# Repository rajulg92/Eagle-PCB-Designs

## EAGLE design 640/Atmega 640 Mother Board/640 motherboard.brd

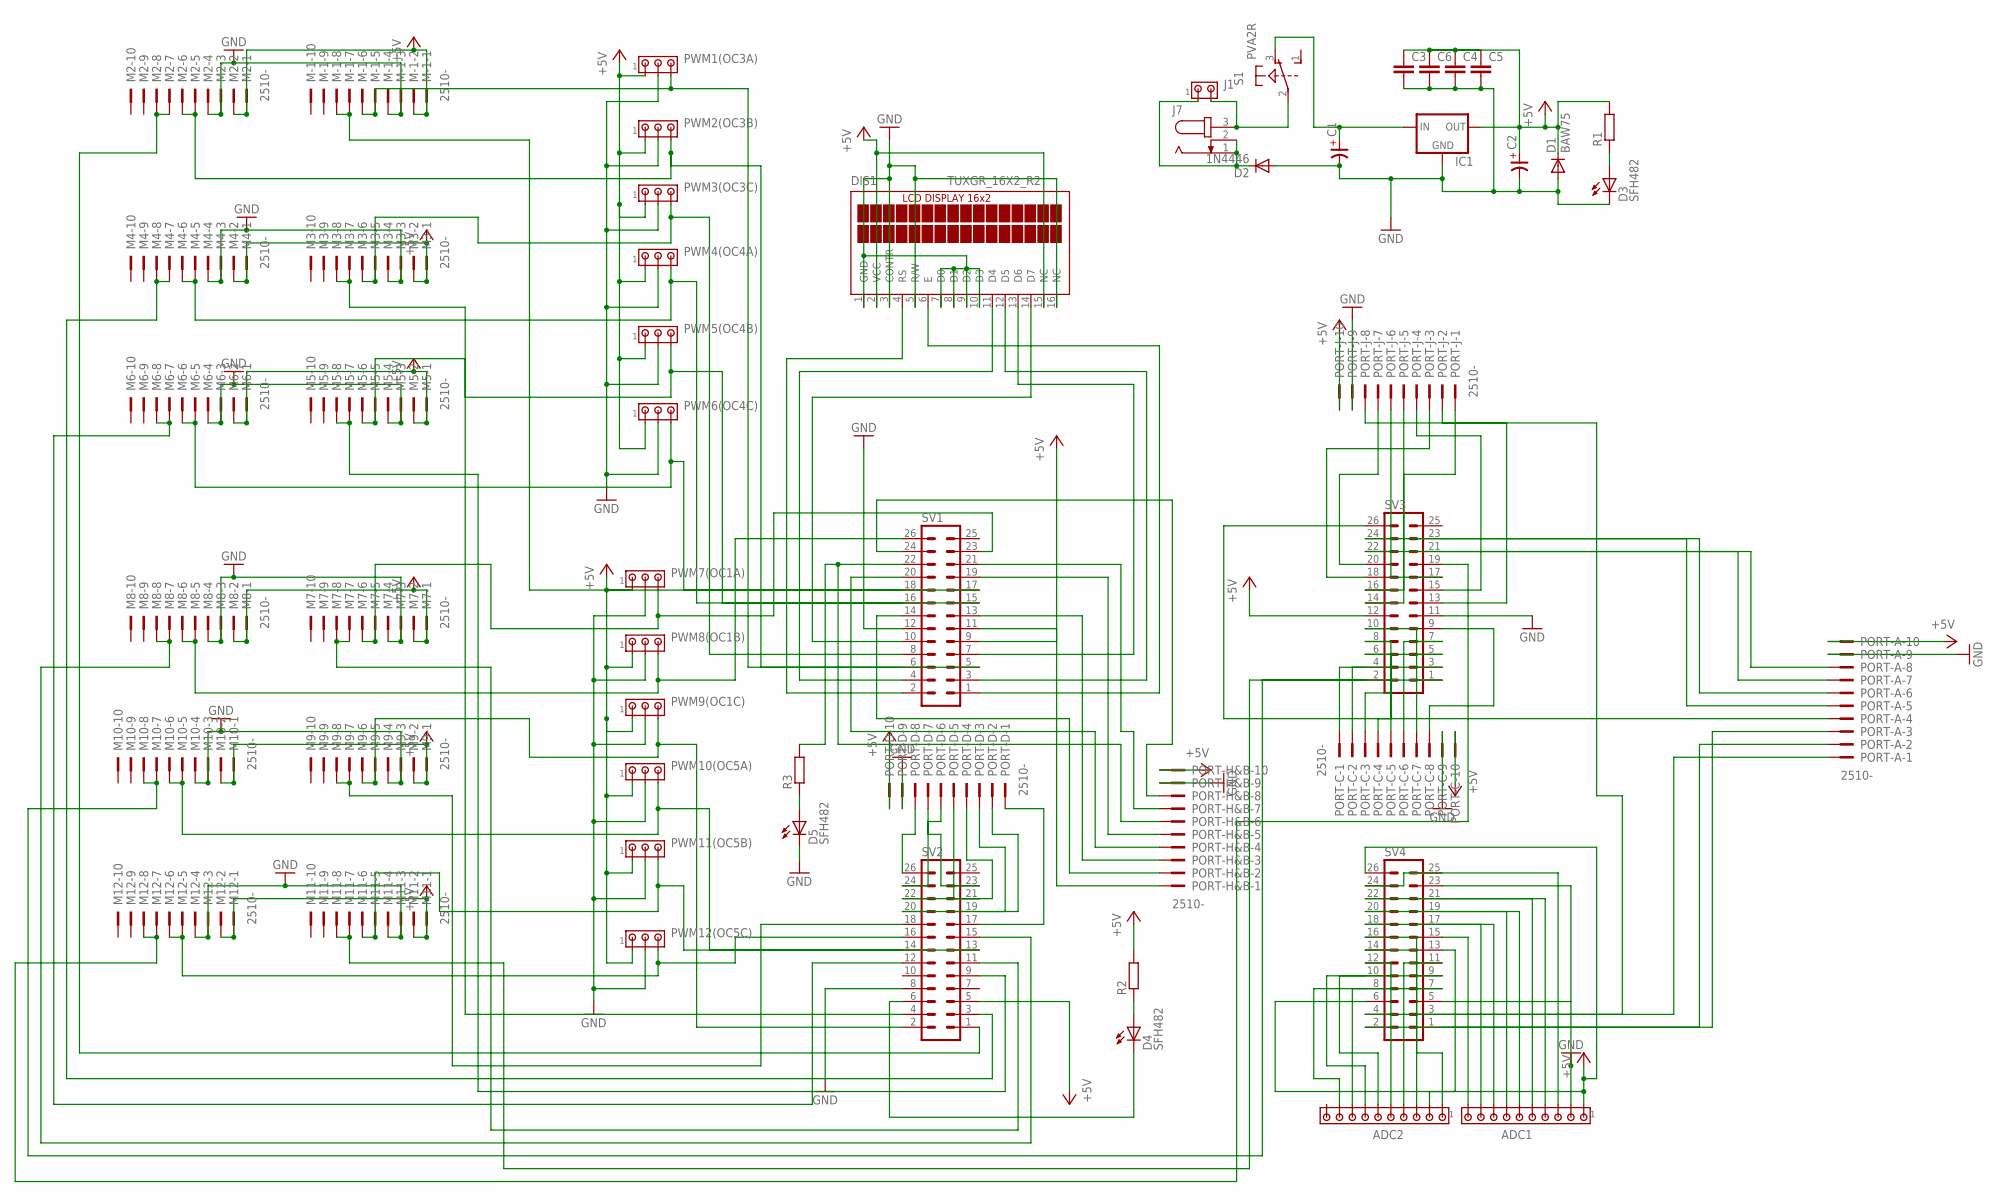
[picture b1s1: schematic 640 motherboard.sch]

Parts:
ADC1, ADC2: MTA10-100; 10X10MTA
C1, C2: CP-E-050X125; E-050X125
C3, C4, C5, C6: C2.5/2; C2.5-2
D1: BAW75; DO35-10
D2: 1N4446; DO35-10
D3, D4, D5: SFH482
DIS1: TUXGR_16X2_R2
IC1: LM323-TO3; TO3-K02
J1: MTA02-156; 1X2MTA
J7: JACK-PLUG1; SPC4078
M2, M3, M4, M5, M6, M7, M8, M9, M10, M11, M12: 2510-; PAK100/2500-10
M-1: 2510-; PAK100/2500-10
PORT-A: 2510-; PAK100/2500-10
PORT-C: 2510-; PAK100/2500-10
PORT-D: 2510-; PAK100/2500-10
PORT-H&B: 2510-; PAK100/2500-10
PORT-J: 2510-; PAK100/2500-10
PWM1(OC3A), PWM2(OC3B), PWM3(OC3C), PWM4(OC4A), PWM5(OC4B), PWM6(OC4C), PWM7(OC1A), PWM8(OC1B), PWM9(OC1C), PWM10(OC5A), PWM11(OC5B), PWM12(OC5C): MTA03-100; 10X03MTA
R1, R2, R3: R-EU_0207/10; 0207/10
S1: PVA2R
SV1, SV2, SV3, SV4: ML26

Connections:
+5V: ADC1.1, C2.+, C3.1, C4.1, C5.1, C6.1, D1.C, DIS1.2 (VCC), DIS1.15 (NC), IC1.1 (OUT), M2.1, M2.2, M3.1, M3.2, M4.1, M4.2, M5.1, M5.2, M6.1, M6.2, M7.1, M7.2, M8.1, M8.2, M9.1, M9.2, M10.1, M10.2, M11.1, M11.2, M12.1, M12.2, M-1.1, M-1.2, PORT-A.10, PORT-C.10, PORT-D.10, PORT-H&B.10, PORT-J.10, PWM1(OC3A).1, PWM2(OC3B).1, PWM3(OC3C).1, PWM4(OC4A).1, PWM5(OC4B).1, PWM6(OC4C).1, PWM7(OC1A).1, PWM8(OC1B).1, PWM9(OC1C).1, PWM10(OC5A).1, PWM11(OC5B).1, PWM12(OC5C).1, R1.2, R2.2, SV1.9, SV2.5, SV3.12, SV4.6, SV4.26
GND: ADC1.2, C1.-, C2.-, C3.2, C4.2, C5.2, C6.2, D1.A, D2.A, D3.K (C), D5.K (C), DIS1.1 (GND), DIS1.3 (CONTR), DIS1.5 (R/W), DIS1.7 (D0), DIS1.8 (D1), DIS1.9 (D2), DIS1.10 (D3), DIS1.16 (NC), IC1.3 (GND), M2.3, M2.4, M3.3, M3.4, M4.3, M4.4, M5.3, M5.4, M6.3, M6.4, M7.3, M7.4, M8.3, M8.4, M9.3, M9.4, M10.3, M10.4, M11.3, M11.4, M12.3, M12.4, M-1.3, M-1.4, PORT-A.9, PORT-C.9, PORT-D.9, PORT-H&B.9, PORT-J.9, PWM1(OC3A).2, PWM2(OC3B).2, PWM3(OC3C).2, PWM4(OC4A).2, PWM5(OC4B).2, PWM6(OC4C).2, PWM7(OC1A).2, PWM8(OC1B).2, PWM9(OC1C).2, PWM10(OC5A).2, PWM11(OC5B).2, PWM12(OC5C).2, SV1.12, SV2.8, SV3.11, SV4.5, SV4.23
unnamed: C1.+, IC1.2 (IN), S1.3 (O)
unnamed: D2.C, J1.1, J7.1, J7.2
unnamed: PORT-C.1, SV3.4
unnamed: M2.5, M2.6, PWM2(OC3B).3, SV1.5
unnamed: M3.5, M3.6, PWM3(OC3C).3, SV1.8
unnamed: M4.5, M4.6, PWM4(OC4A).3, SV1.16
unnamed: M5.5, M5.6, PWM5(OC4B).3, SV1.15
unnamed: M6.5, M6.6, PWM6(OC4C).3, SV1.18
unnamed: M12.5, M12.6, PWM12(OC5C).3, SV2.16
unnamed: PORT-C.2, SV3.3
unnamed: M10.5, M10.6, PWM10(OC5A).3, SV2.14
unnamed: M9.5, M9.6, PWM9(OC1C).3, SV2.2
unnamed: M8.5, M8.6, PWM8(OC1B).3, SV1.26
unnamed: M7.5, M7.6, PWM7(OC1A).3, SV1.23
unnamed: ADC1.4, SV4.21
unnamed: ADC1.5, SV4.22
unnamed: ADC1.3, SV4.24
unnamed: ADC1.6, SV4.19
unnamed: ADC1.7, SV4.20
unnamed: ADC1.8, SV4.17
unnamed: ADC1.9, SV4.18
unnamed: ADC1.10, SV4.15
unnamed: ADC2.1, SV4.16
unnamed: ADC2.2, SV4.13
unnamed: ADC2.3, SV4.14
unnamed: ADC2.4, SV4.11
unnamed: ADC2.5, SV4.12
unnamed: ADC2.7, SV4.10
unnamed: ADC2.6, SV4.9
unnamed: ADC2.9, SV4.8
unnamed: M-1.5, M-1.6, PWM1(OC3A).3, SV1.6
unnamed: M11.5, M11.6, PWM11(OC5B).3, SV2.13
unnamed: PORT-C.3, SV3.6
unnamed: PORT-C.4, SV3.5
unnamed: PORT-C.5, SV3.8
unnamed: PORT-C.6, SV3.7
unnamed: PORT-C.7, SV3.10
unnamed: PORT-C.8, SV3.9
unnamed: PORT-J.1, SV3.14
unnamed: PORT-J.2, SV3.13
unnamed: PORT-J.3, SV3.16
unnamed: PORT-J.4, SV3.15
unnamed: PORT-J.5, SV3.18
unnamed: PORT-J.6, SV3.17
unnamed: PORT-J.7, SV3.20
unnamed: PORT-J.8, SV4.3
unnamed: ADC2.8, SV4.7
unnamed: PORT-A.1, SV4.4
unnamed: PORT-A.2, SV4.1
unnamed: PORT-A.3, SV4.2
unnamed: PORT-A.4, SV3.26
unnamed: PORT-A.5, SV3.23
unnamed: PORT-A.6, SV3.24
unnamed: PORT-A.7, SV3.21
unnamed: PORT-A.8, SV3.22
unnamed: PORT-D.8, SV2.26
unnamed: PORT-D.7, SV2.23
unnamed: PORT-D.6, SV2.24
unnamed: PORT-D.5, SV2.21
unnamed: PORT-D.2, SV2.20
unnamed: PORT-D.3, SV2.19
unnamed: PORT-D.4, SV2.22
unnamed: PORT-D.1, SV2.17
unnamed: D3.A, R1.1
unnamed: J1.2, J7.3, S1.2
unnamed: DIS1.11 (D4), SV1.4
unnamed: DIS1.12 (D5), SV1.3
unnamed: DIS1.13 (D6), SV1.7
unnamed: DIS1.14 (D7), SV1.10
unnamed: DIS1.4 (RS), SV1.2
unnamed: DIS1.6 (E), SV1.1
unnamed: PORT-H&B.1, SV1.11
unnamed: M2.7, M2.8, SV2.1
unnamed: PORT-H&B.2, SV1.14
unnamed: PORT-H&B.3, SV1.13
unnamed: PORT-H&B.4, SV1.20
unnamed: M3.7, M3.8, SV2.4
unnamed: PORT-H&B.5, SV1.19
unnamed: M-1.7, M-1.8, SV1.17
unnamed: M5.7, M5.8, SV2.9
unnamed: M4.7, M4.8, SV2.3
unnamed: PORT-H&B.6, R3.2, SV1.22
unnamed: PORT-H&B.7, SV1.21
unnamed: M7.7, M7.8, SV2.11
unnamed: M6.7, M6.8, SV2.12
unnamed: PORT-H&B.8, SV1.24
unnamed: D4.A, R2.1
unnamed: M9.7, M9.8, SV2.18
unnamed: M8.7, M8.8, SV2.15
unnamed: M11.7, M11.8, SV3.1
unnamed: D4.K (C), SV2.6
unnamed: M10.7, M10.8, SV3.2
unnamed: M12.7, M12.8, SV3.19
unnamed: D5.A, R3.1

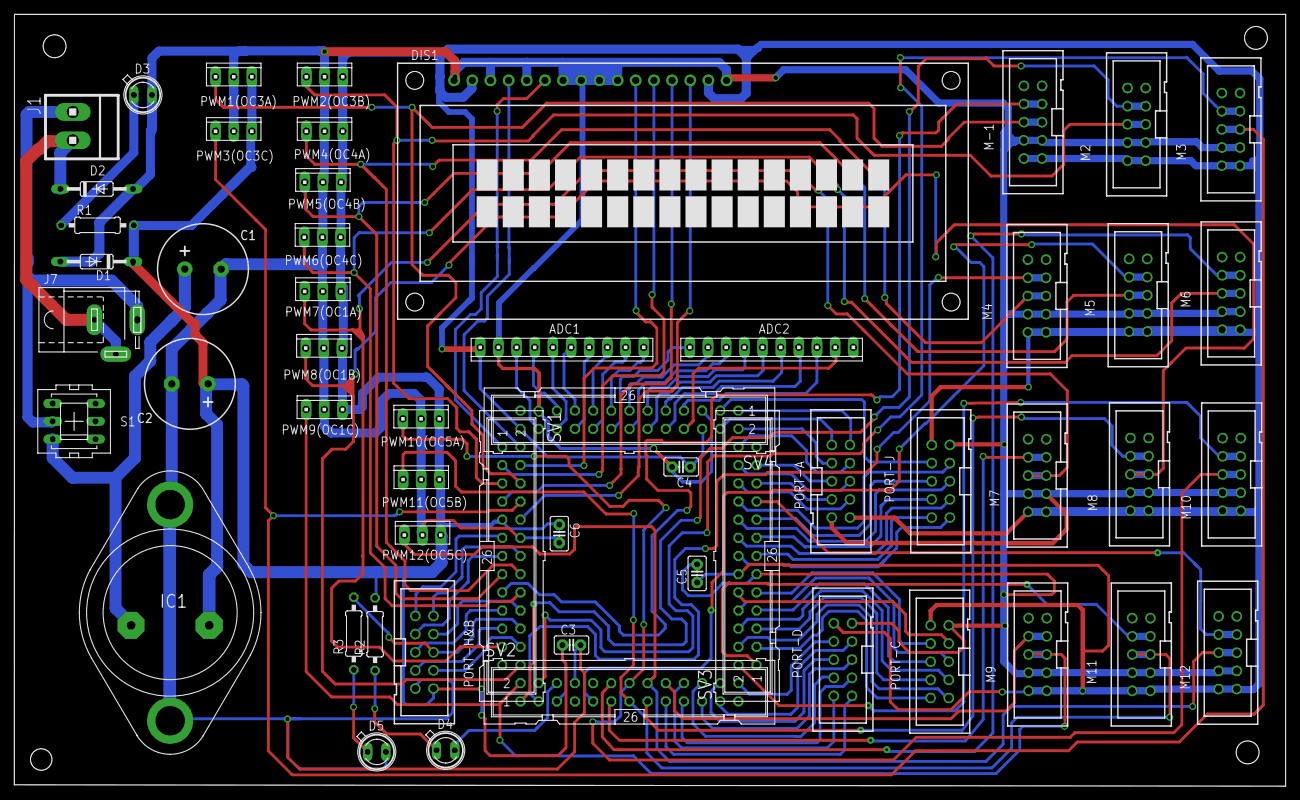
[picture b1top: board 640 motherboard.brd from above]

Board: 2 copper layers, 177.8 x 107.9 mm, 54 parts (0 on the bottom side), 96 nets.

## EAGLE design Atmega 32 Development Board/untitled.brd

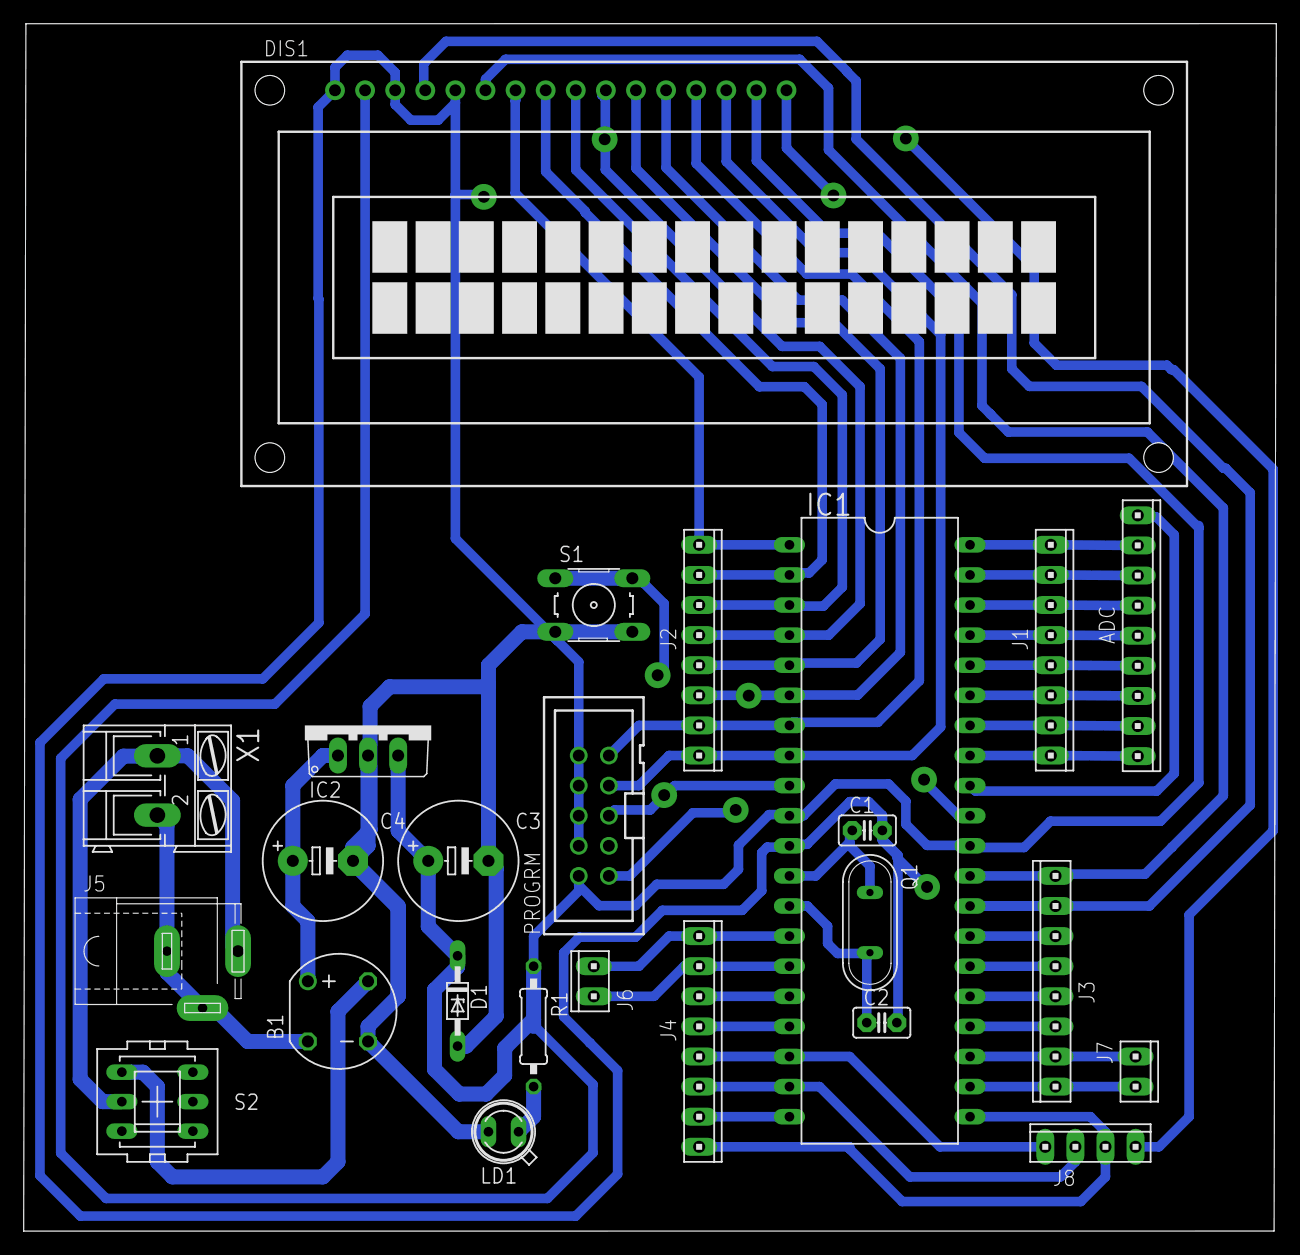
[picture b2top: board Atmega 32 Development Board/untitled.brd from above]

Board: 2 copper layers, 105.7 x 101.9 mm, 25 parts (0 on the bottom side), 43 nets.

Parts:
ADC: 10X09MTA
B1: RB1A
C1, C2: C2.5-2
C3, C4: E5-10,5
D1: BZX90; DO34Z7
DIS1: TUXGR_16X2_R2
IC1: MEGA323-P; DIL40
IC2: 7805TV; TO220V
J1, J2, J3, J4: 10X08MTA
J5: SPC4078
J6, J7: 10X02MTA
J8: 10X04MTA
LD1: SFH482
PROGRM: 2510-; PAK100/2500-10
Q1: QS
R1: 0207/10
S1: B3F-10XX
S2: PVA2R
X1: AK300/2

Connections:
GND: B1.-, C1.2, C2.2, C3.-, C4.-, D1.A, DIS1.1, DIS1.3, DIS1.5, DIS1.16, IC1.11, IC1.31, IC2.2, LD1.K, PROGRM.4, PROGRM.6, PROGRM.8, PROGRM.10, S1.3, S1.4
unnamed: B1.AC2, J5.1, J5.2, X1.2
unnamed: J5.3, S2.2, X1.1
unnamed: B1.AC1, S2.1
unnamed: B1.+, C4.+, IC2.1
unnamed: ADC.9, IC1.32
unnamed: DIS1.14, IC1.8, J2.1, PROGRM.7
unnamed: C1.1, IC1.12, Q1.1
unnamed: C2.1, IC1.13, Q1.2
unnamed: DIS1.13, IC1.7, J2.2, PROGRM.9
unnamed: ADC.1, IC1.33, J1.1
unnamed: ADC.2, IC1.34, J1.2
unnamed: ADC.3, IC1.35, J1.3
unnamed: ADC.4, IC1.36, J1.4
unnamed: ADC.5, IC1.37, J1.5
unnamed: ADC.6, IC1.38, J1.6
unnamed: ADC.7, IC1.39, J1.7
unnamed: ADC.8, IC1.40, J1.8
unnamed: DIS1.11, IC1.5, J2.4
unnamed: DIS1.10, IC1.4, J2.5, J8.1
unnamed: DIS1.9, IC1.3, J2.6
unnamed: DIS1.8, IC1.2, J2.7
unnamed: DIS1.7, IC1.1, J2.8
unnamed: DIS1.6, IC1.29, J3.1
unnamed: DIS1.4, IC1.28, J3.2
unnamed: IC1.27, J3.3
unnamed: IC1.26, J3.4
unnamed: IC1.25, J3.5
unnamed: IC1.24, J3.6
unnamed: IC1.23, J3.7, J7.2
unnamed: IC1.22, J3.8, J7.1
unnamed: IC1.21, J4.1, J8.2
unnamed: IC1.20, J4.2
unnamed: IC1.19, J4.3, J8.3
unnamed: IC1.18, J4.4, J8.4
unnamed: IC1.17, J4.5
unnamed: IC1.16, J4.6
unnamed: IC1.15, J4.7, J6.2
unnamed: IC1.14, J4.8, J6.1
unnamed: IC1.9, PROGRM.5, S1.1, S1.2
unnamed: DIS1.12, IC1.6, J2.3, PROGRM.1
unnamed: LD1.A, R1.2
VCC: C3.+, D1.C, DIS1.2, DIS1.15, IC1.10, IC1.30, IC2.3, PROGRM.2, R1.1

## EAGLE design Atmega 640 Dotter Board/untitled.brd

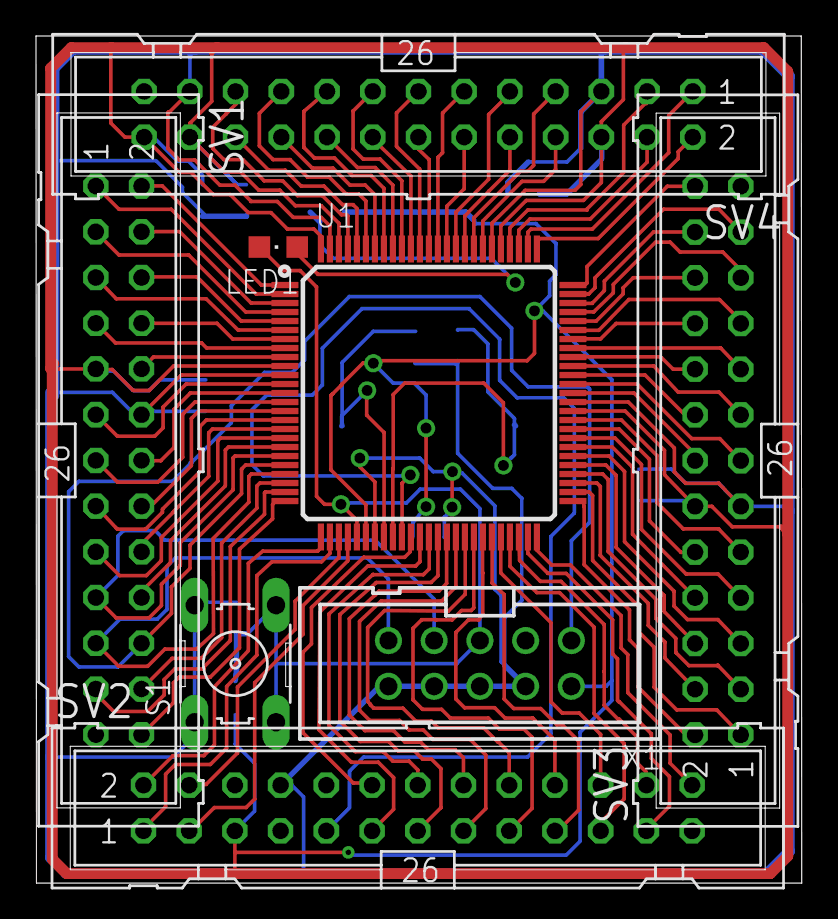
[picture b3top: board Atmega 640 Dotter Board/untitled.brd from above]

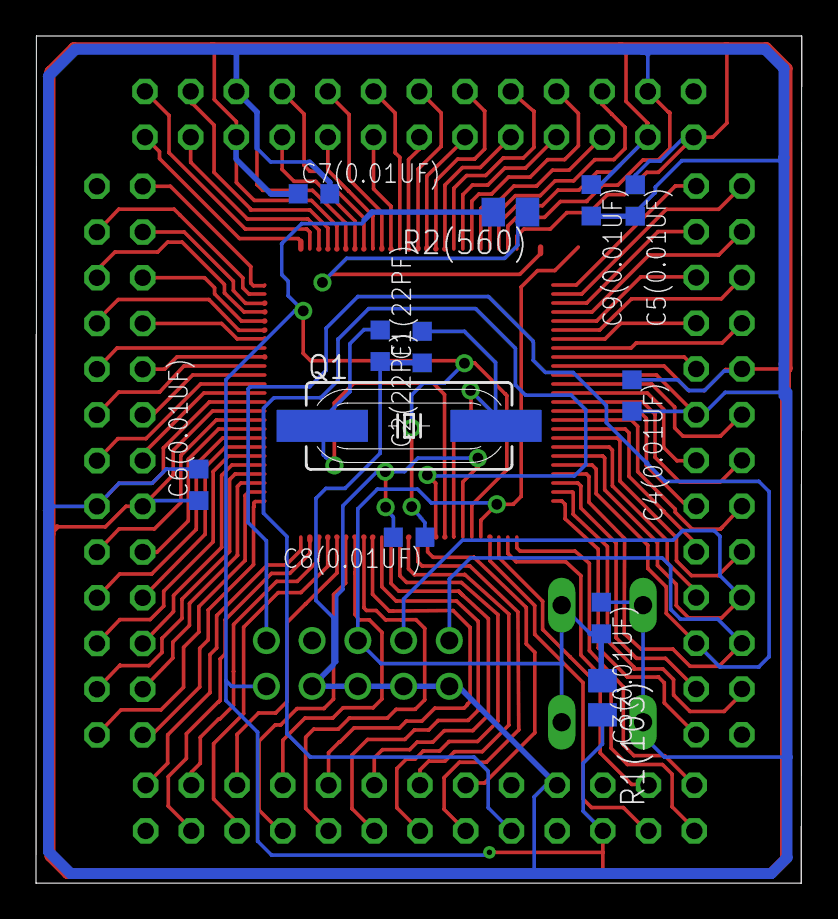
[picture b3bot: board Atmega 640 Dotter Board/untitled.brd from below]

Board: 2 copper layers, 42.5 x 47.1 mm, 20 parts (12 on the bottom side), 92 nets.

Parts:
C1(22PF), C2(22PF), C3(0.01UF), C4(0.01UF), C5(0.01UF), C6(0.01UF), C7(0.01UF), C8(0.01UF), C9(0.01UF): C0603K
LED1: CHIPLED_0805
Q1: SM49
R1(103), R2(560): M2012
S1: B3F-10XX
SV1, SV2, SV3, SV4: ML26
U1: TQFP100
X1: 2510-; PAK100/2500-10

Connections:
unnamed: SV3.14, U1.63
unnamed: C2(22PF).1, Q1.1, U1.34
unnamed: SV2.16, U1.40
unnamed: SV1.20, U1.19
unnamed: SV1.1, U1.2
unnamed: SV3.13, U1.64
unnamed: SV1.3, U1.4
unnamed: SV1.4, U1.3
unnamed: SV1.6, U1.5
unnamed: SV1.5, U1.6
unnamed: SV1.8, U1.7
unnamed: SV1.7, U1.8
unnamed: SV1.10, U1.9
unnamed: SV1.19, U1.20, X1.7
unnamed: SV1.11, U1.12
unnamed: SV1.14, U1.13
unnamed: SV1.13, U1.14
unnamed: SV1.16, U1.15
unnamed: SV1.15, U1.16
unnamed: SV1.18, U1.17
unnamed: SV1.17, U1.18
unnamed: SV1.22, U1.21, X1.1
unnamed: SV1.21, U1.22, X1.9
unnamed: SV1.24, U1.23
unnamed: SV1.23, U1.24
unnamed: SV1.26, U1.25
unnamed: SV2.2, U1.26
unnamed: SV2.1, U1.27
unnamed: SV2.4, U1.28
unnamed: SV2.3, U1.29
unnamed: SV2.9, U1.35
unnamed: SV2.12, U1.36
unnamed: SV2.11, U1.37
unnamed: SV2.14, U1.38
unnamed: SV2.13, U1.39
unnamed: SV2.15, U1.41
unnamed: SV2.18, U1.42
unnamed: SV2.17, U1.43
unnamed: SV2.20, U1.44
unnamed: SV2.19, U1.45
unnamed: SV2.22, U1.46
unnamed: SV2.21, U1.47
unnamed: SV2.24, U1.48
unnamed: SV2.23, U1.49
unnamed: SV2.26, U1.50
unnamed: C1(22PF).2, Q1.2, U1.33
unnamed: SV3.2, U1.51
unnamed: SV3.1, U1.52
unnamed: SV3.4, U1.53
unnamed: SV3.3, U1.54
unnamed: SV3.6, U1.55
unnamed: SV3.5, U1.56
unnamed: SV3.8, U1.57
unnamed: SV3.7, U1.58
unnamed: SV3.10, U1.59
unnamed: SV3.9, U1.60
unnamed: SV4.18, U1.92
unnamed: SV3.16, U1.65
unnamed: SV3.15, U1.66
unnamed: SV3.18, U1.67
unnamed: SV3.17, U1.68
unnamed: SV3.20, U1.69
unnamed: SV3.19, U1.70
unnamed: SV3.22, U1.71
unnamed: SV3.21, U1.72
unnamed: SV3.24, U1.73
unnamed: SV3.23, U1.74
unnamed: SV3.26, U1.75
unnamed: SV4.2, U1.76
unnamed: SV4.1, U1.77
unnamed: SV4.4, U1.78
unnamed: SV4.3, U1.79
unnamed: SV4.19, U1.95
unnamed: SV4.7, U1.83
unnamed: SV4.8, U1.82
unnamed: SV4.9, U1.85
unnamed: SV4.10, U1.84
unnamed: SV4.11, U1.87
unnamed: SV4.12, U1.86
unnamed: SV4.13, U1.89
unnamed: SV4.14, U1.88
unnamed: SV4.15, U1.91
unnamed: SV4.16, U1.90
unnamed: SV4.17, U1.93
unnamed: SV4.20, U1.94
unnamed: SV4.21, U1.97
unnamed: SV4.22, U1.96
unnamed: C4(0.01UF).1, C5(0.01UF).1, C6(0.01UF).1, C7(0.01UF).1, C8(0.01UF).1, C9(0.01UF).1, R1(103).2, R2(560).2, SV1.9, SV2.5, SV3.12, SV4.6, SV4.24, SV4.26, U1.10, U1.31, U1.61, U1.80, U1.98, U1.100, X1.2
unnamed: SV1.2, U1.1
unnamed: C3(0.01UF).2, LED1.C, R1(103).1, S1.3, S1.4, U1.30, X1.5
unnamed: C1(22PF).1, C2(22PF).2, C3(0.01UF).1, C4(0.01UF).2, C5(0.01UF).2, C6(0.01UF).2, C7(0.01UF).2, C8(0.01UF).2, C9(0.01UF).2, S1.1, S1.2, SV1.12, SV2.8, SV3.11, SV4.5, SV4.23, U1.11, U1.32, U1.62, U1.81, U1.99, X1.4, X1.6, X1.8, X1.10
unnamed: LED1.A, R2(560).1

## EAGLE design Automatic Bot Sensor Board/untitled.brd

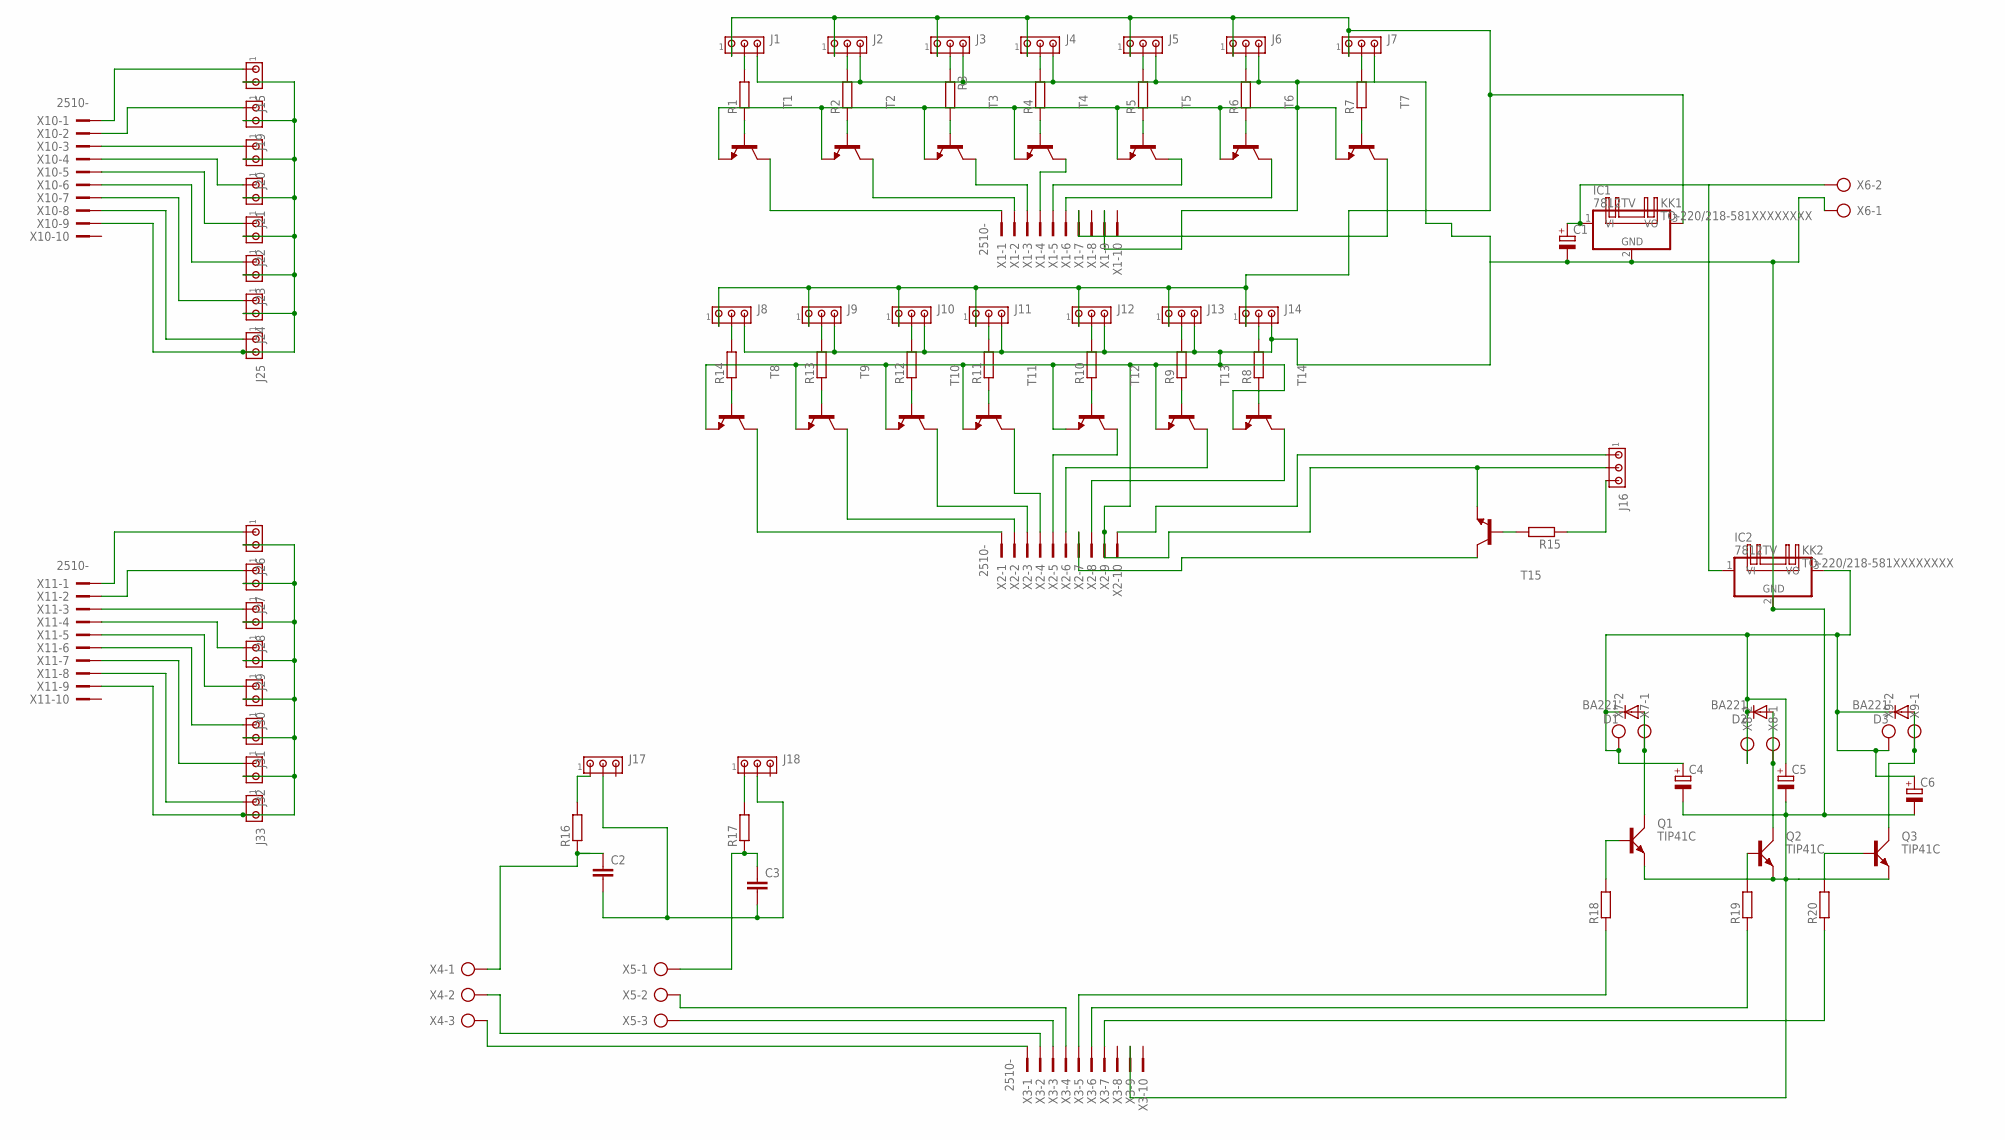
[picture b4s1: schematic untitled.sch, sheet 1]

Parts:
C1: CPOL-EUE5-10.5; E5-10,5
C2, C3: C-EU375-192X418; C375-192X418
C4, C5, C6: CPOL-EUE5-13; E5-13
D1, D2, D3: BA221; DO35-10
IC1, IC2: 7812TV; TO220V
J1, J2, J3, J4, J5, J6, J7, J8, J9, J10, J11, J12, J13, J14, J16, J17, J18: MTA03-100; 10X03MTA
J15, J19, J20, J21, J22, J23, J24, J25, J26, J27, J28, J29, J30, J31, J32, J33: MTA02-100; 10X02MTA
KK1, KK2: TO-220/218-581XXXXXXXX; 581XXXXXXXX
Q1, Q2, Q3: TIP41C; TO220AV
R1, R2, R3, R4, R5, R6, R7, R8, R9, R10, R11, R12, R13, R14, R15, R16, R17, R18, R19, R20: R-EU_0207/10; 0207/10
T1, T2, T3, T4, T5, T6, T7, T8, T9, T10, T11, T12, T13, T14, T15: 2N5401-NPN-TO92-CBE; TO92-CBE
X1, X2, X3, X10, X11: 2510-; PAK100/2500-10
X4, X5: AK300/3
X6, X7, X8, X9: AK300/2

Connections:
unnamed: R3.2, T3.B
unnamed: R1.1, T1.B
unnamed: J2.2, R2.2
unnamed: J8.2, R14.2
unnamed: J1.2, R1.2
unnamed: R2.1, T2.B
unnamed: J3.2, R3.1
unnamed: J4.2, R4.2
unnamed: R4.1, T4.B
unnamed: R5.1, T5.B
unnamed: J5.2, R5.2
unnamed: J6.2, R6.2
unnamed: R6.1, T6.B
unnamed: J7.2, R7.2
unnamed: R7.1, T7.B
unnamed: J13.2, R9.2
unnamed: R9.1, T13.B
unnamed: R8.1, T14.B
unnamed: J14.2, R8.2
unnamed: J12.2, R10.2
unnamed: R10.1, T12.B
unnamed: R11.1, T11.B
unnamed: J11.2, R11.2
unnamed: J10.2, R12.2
unnamed: R12.1, T10.B
unnamed: R13.1, T9.B
unnamed: J9.2, R13.2
unnamed: R14.1, T8.B
unnamed: T5.C, X1.5
unnamed: T8.C, X2.1
unnamed: T9.C, X2.2
unnamed: T1.C, X1.1
unnamed: T10.C, X2.3
unnamed: T11.C, X2.4
unnamed: T12.C, X2.5
unnamed: T13.C, X2.6
unnamed: J16.1, X2.10
unnamed: T2.C, X1.2
unnamed: T3.C, X1.3
unnamed: T4.C, X1.4
unnamed: T6.C, X1.6
unnamed: T7.C, X1.7
unnamed: D1.A, Q1.C, X7.1
unnamed: IC1.3 (VO), J1.1, J2.1, J3.1, J4.1, J5.1, J6.1, J7.1, J8.1, J9.1, J10.1, J11.1, J12.1, J13.1, J14.1
unnamed: T14.C, X2.8
unnamed: C1.+, IC1.1 (VI), IC2.1 (VI), X6.2
unnamed: J16.3, R15.1
unnamed: R15.2, T15.B
unnamed: T15.C, X2.7
unnamed: Q1.B, R18.2
unnamed: D2.A, Q2.C, X8.1
unnamed: Q2.B, R19.2
unnamed: Q3.B, R20.2
unnamed: C1.-, C4.-, C5.-, C6.-, IC1.2 (GND), IC2.2 (GND), J1.3, J2.3, J3.3, J4.3, J5.3, J6.3, J7.3, J8.3, J9.3, J10.3, J11.3, J12.3, J13.3, J14.3, J16.2, Q1.E, Q2.E, Q3.E, T1.E, T2.E, T3.E, T4.E, T5.E, T6.E, T7.E, T8.E, T9.E, T10.E, T11.E, T12.E, T13.E, T14.E, T15.E, X1.9, X2.9, X3.9, X6.1
unnamed: D3.A, Q3.C, X9.1
unnamed: J17.1, R16.2
unnamed: C4.+, C5.+, C6.+, D1.C, D2.C, D3.C, IC2.3 (VO), X7.2, X8.2, X9.2
unnamed: C2.1, R16.1, X4.1
unnamed: J18.1, R17.2
unnamed: C3.1, R17.1, X5.1
unnamed: C2.2, C3.2, J17.2, J18.2
unnamed: J15.1, X10.1
unnamed: J19.1, X10.2
unnamed: X3.1, X4.3
unnamed: X3.2, X4.2
unnamed: X3.3, X5.3
unnamed: X3.4, X5.2
unnamed: R18.1, X3.5
unnamed: R19.1, X3.6
unnamed: R20.1, X3.7
unnamed: J20.1, X10.3
unnamed: J21.1, X10.4
unnamed: J22.1, X10.5
unnamed: J23.1, X10.6
unnamed: J24.1, X10.7
unnamed: J25.1, X10.8
unnamed: J15.2, J19.2, J20.2, J21.2, J22.2, J23.2, J24.2, J25.2, X10.9
unnamed: J26.1, X11.1
unnamed: J27.1, X11.2
unnamed: J28.1, X11.3
unnamed: J29.1, X11.4
unnamed: J30.1, X11.5
unnamed: J31.1, X11.6
unnamed: J32.1, X11.7
unnamed: J33.1, X11.8
unnamed: J26.2, J27.2, J28.2, J29.2, J30.2, J31.2, J32.2, J33.2, X11.9

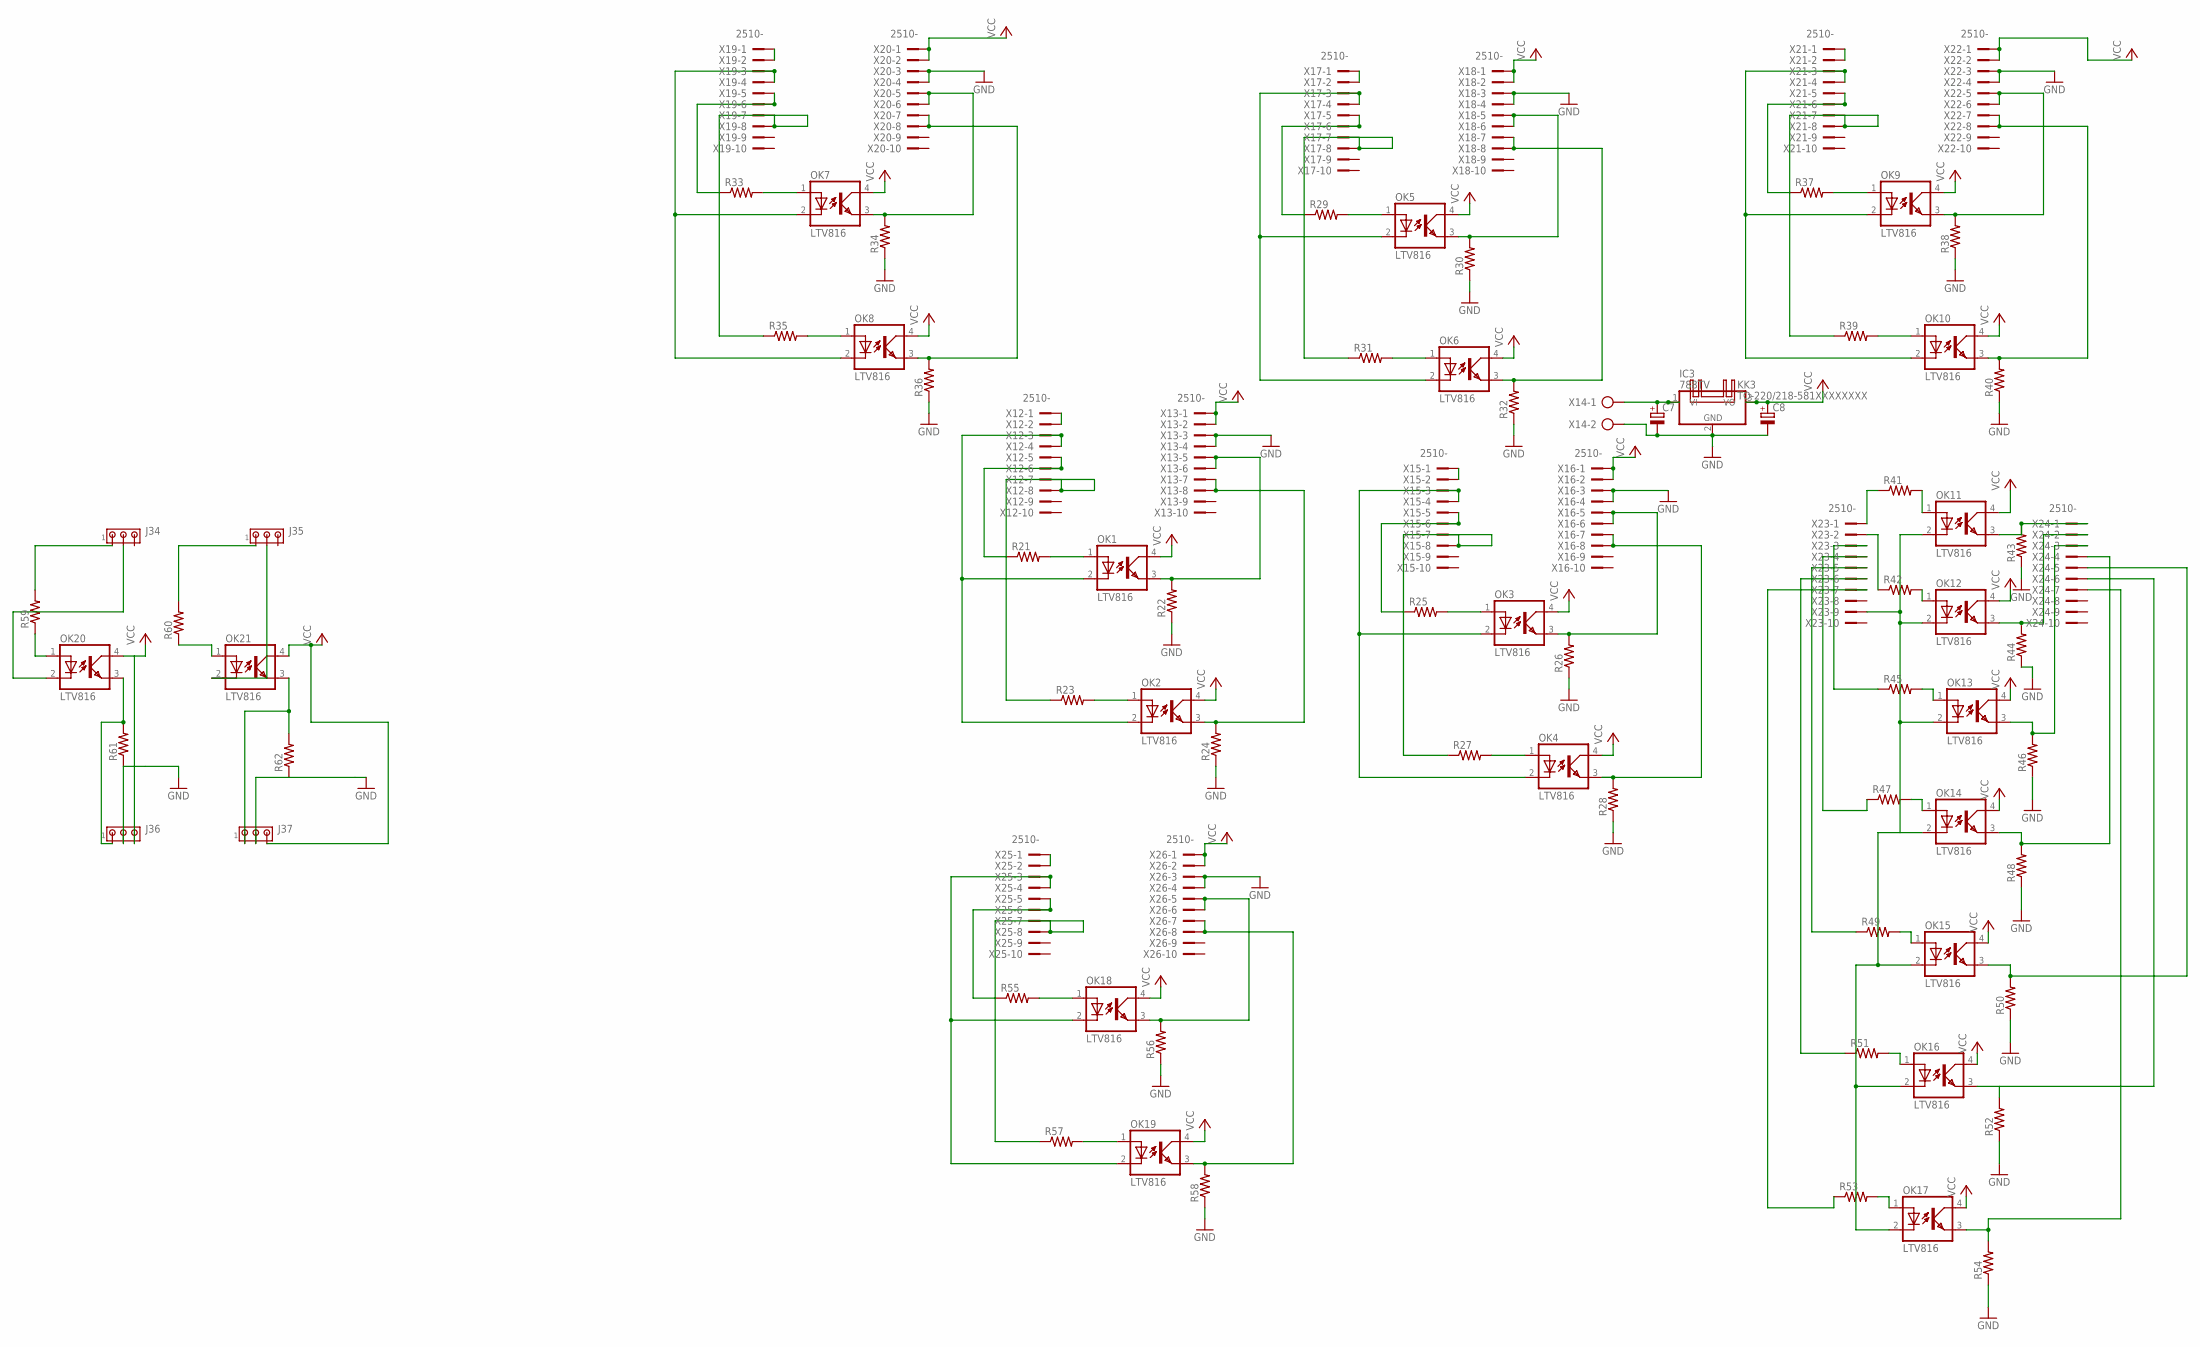
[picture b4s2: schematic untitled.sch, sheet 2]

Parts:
C7: CPOL-EUE5-13; E5-13
C8: CPOL-EUE5-10.5; E5-10,5
IC3: 788TV; TO220V
J34, J35, J36, J37: MTA03-100; 10X03MTA
KK3: TO-220/218-581XXXXXXXX; 581XXXXXXXX
OK1, OK2, OK3, OK4, OK5, OK6, OK7, OK8, OK9, OK10, OK11, OK12, OK13, OK14, OK15, OK16, OK17, OK18, OK19, OK20, OK21: LTV816; DIL04
R21, R22, R23, R24, R25, R26, R27, R28, R29, R30, R31, R32, R33, R34, R35, R36, R37, R38, R39, R40, R41, R42, R43, R44, R45, R46, R47, R48, R49, R50, R51, R52, R53, R54, R55, R56, R57, R58, R59, R60, R61, R62: R-US_0207/10; 0207/10
X12, X13, X15, X16, X17, X18, X19, X20, X21, X22, X23, X24, X25, X26: 2510-; PAK100/2500-10
X14: AK300/2

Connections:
GND: C7.-, C8.-, IC3.2 (GND), J36.2, J37.2, R22.1, R24.1, R26.1, R28.1, R30.1, R32.1, R34.1, R36.1, R38.1, R40.1, R43.1, R44.1, R46.1, R48.1, R50.1, R52.1, R54.1, R56.1, R58.1, R61.1, R62.1, X13.3, X13.4, X14.2, X16.3, X16.4, X18.3, X18.4, X20.3, X20.4, X22.3, X22.4, X26.3, X26.4
unnamed: X12.1, X12.2
unnamed: R21.1, X12.5, X12.6
unnamed: C7.+, IC3.1 (VI), X14.1
unnamed: OK1.1 (A), R21.2
unnamed: OK1.3 (EMIT), R22.2, X13.5, X13.6
unnamed: OK1.2 (C), OK2.2 (C), X12.3, X12.4
unnamed: R23.1, X12.7, X12.8
unnamed: OK2.1 (A), R23.2
unnamed: OK2.3 (EMIT), R24.2, X13.7, X13.8
unnamed: X15.1, X15.2
unnamed: R25.1, X15.5, X15.6
unnamed: OK3.1 (A), R25.2
unnamed: OK3.3 (EMIT), R26.2, X16.5, X16.6
unnamed: OK3.2 (C), OK4.2 (C), X15.3, X15.4
unnamed: R27.1, X15.7, X15.8
unnamed: OK4.1 (A), R27.2
unnamed: OK4.3 (EMIT), R28.2, X16.7, X16.8
unnamed: X17.1, X17.2
unnamed: R29.1, X17.5, X17.6
unnamed: OK5.1 (A), R29.2
unnamed: OK5.3 (EMIT), R30.2, X18.5, X18.6
unnamed: OK5.2 (C), OK6.2 (C), X17.3, X17.4
unnamed: R31.1, X17.7, X17.8
unnamed: OK6.1 (A), R31.2
unnamed: OK6.3 (EMIT), R32.2, X18.7, X18.8
unnamed: X19.1, X19.2
unnamed: R33.1, X19.5, X19.6
unnamed: OK7.1 (A), R33.2
unnamed: OK7.3 (EMIT), R34.2, X20.5, X20.6
unnamed: OK7.2 (C), OK8.2 (C), X19.3, X19.4
unnamed: R35.1, X19.7, X19.8
unnamed: OK8.1 (A), R35.2
unnamed: OK8.3 (EMIT), R36.2, X20.7, X20.8
unnamed: X21.1, X21.2
unnamed: R37.1, X21.5, X21.6
unnamed: OK9.1 (A), R37.2
unnamed: OK9.3 (EMIT), R38.2, X22.5, X22.6
unnamed: OK9.2 (C), OK10.2 (C), X21.3, X21.4
unnamed: R39.1, X21.7, X21.8
unnamed: OK10.1 (A), R39.2
unnamed: OK10.3 (EMIT), R40.2, X22.7, X22.8
unnamed: R41.1, X23.1
unnamed: OK11.1 (A), R41.2
unnamed: R42.1, X23.2
unnamed: OK12.1 (A), R42.2
unnamed: R45.1, X23.3
unnamed: OK13.1 (A), R45.2
unnamed: OK11.3 (EMIT), R43.2, X24.1
unnamed: OK12.3 (EMIT), R44.2, X24.2
unnamed: OK13.3 (EMIT), R46.2, X24.3
unnamed: OK14.1 (A), R47.2
unnamed: OK14.3 (EMIT), R48.2, X24.4
unnamed: OK15.1 (A), R49.2
unnamed: OK15.3 (EMIT), R50.2, X24.5
unnamed: OK16.1 (A), R51.2
unnamed: OK17.1 (A), R53.2
unnamed: OK11.2 (C), OK12.2 (C), OK13.2 (C), OK14.2 (C), OK15.2 (C), OK16.2 (C), OK17.2 (C), X23.9
unnamed: OK17.3 (EMIT), R54.2, X24.7
unnamed: R47.1, X23.4
unnamed: R49.1, X23.5
unnamed: R51.1, X23.6
unnamed: R53.1, X23.7
unnamed: OK16.3 (EMIT), R52.2, X24.6
unnamed: X25.1, X25.2
unnamed: R55.1, X25.5, X25.6
unnamed: OK18.1 (A), R55.2
unnamed: OK18.3 (EMIT), R56.2, X26.5, X26.6
unnamed: OK18.2 (C), OK19.2 (C), X25.3, X25.4
unnamed: R57.1, X25.7, X25.8
unnamed: OK19.1 (A), R57.2
unnamed: OK19.3 (EMIT), R58.2, X26.7, X26.8
unnamed: J34.1, R59.2
unnamed: OK20.1 (A), R59.1
unnamed: J34.2, OK20.2 (C)
unnamed: J36.1, OK20.3 (EMIT), R61.2
unnamed: J35.1, R60.2
unnamed: OK21.1 (A), R60.1
unnamed: J35.2, OK21.2 (C)
unnamed: J37.1, OK21.3 (EMIT), R62.2
VCC: C8.+, IC3.3 (VO), J36.3, J37.3, OK1.4 (COL), OK2.4 (COL), OK3.4 (COL), OK4.4 (COL), OK5.4 (COL), OK6.4 (COL), OK7.4 (COL), OK8.4 (COL), OK9.4 (COL), OK10.4 (COL), OK11.4 (COL), OK12.4 (COL), OK13.4 (COL), OK14.4 (COL), OK15.4 (COL), OK16.4 (COL), OK17.4 (COL), OK18.4 (COL), OK19.4 (COL), OK20.4 (COL), OK21.4 (COL), X13.1, X13.2, X16.1, X16.2, X18.1, X18.2, X20.1, X20.2, X22.1, X22.2, X26.1, X26.2

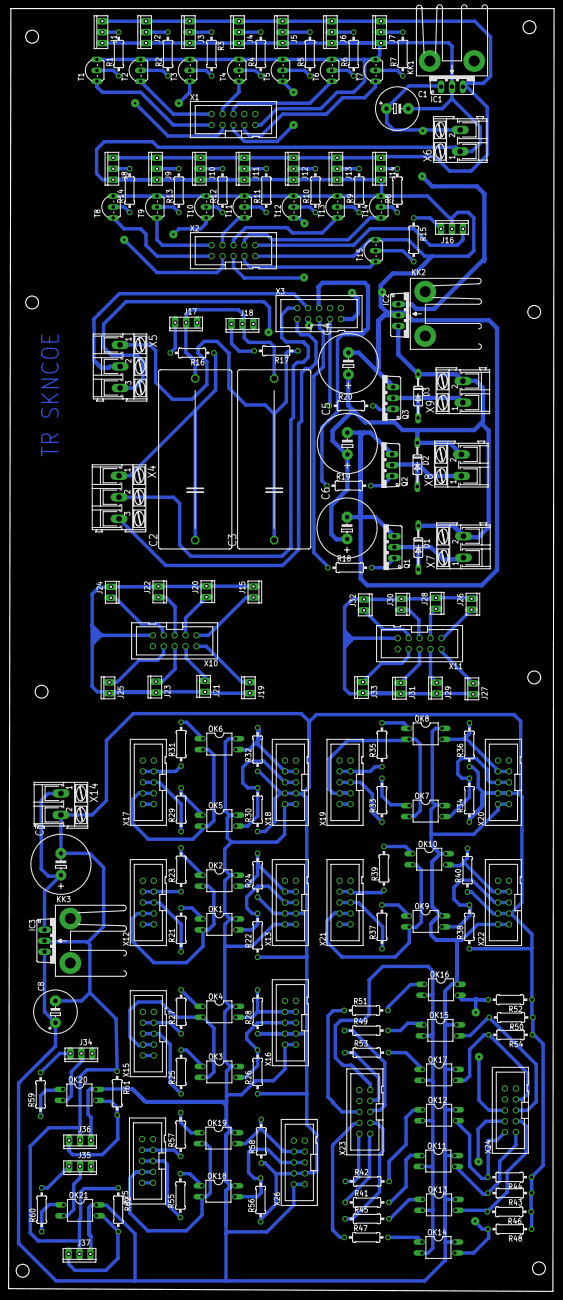
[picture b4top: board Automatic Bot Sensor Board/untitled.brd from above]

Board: 2 copper layers, 126.8 x 298.2 mm, 181 parts (0 on the bottom side), 167 nets.

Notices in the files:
parts and their libraries:
heatsink-aavid: Copyright (C) 2004, Bob Starr (bobstarr@mindspring.com)
